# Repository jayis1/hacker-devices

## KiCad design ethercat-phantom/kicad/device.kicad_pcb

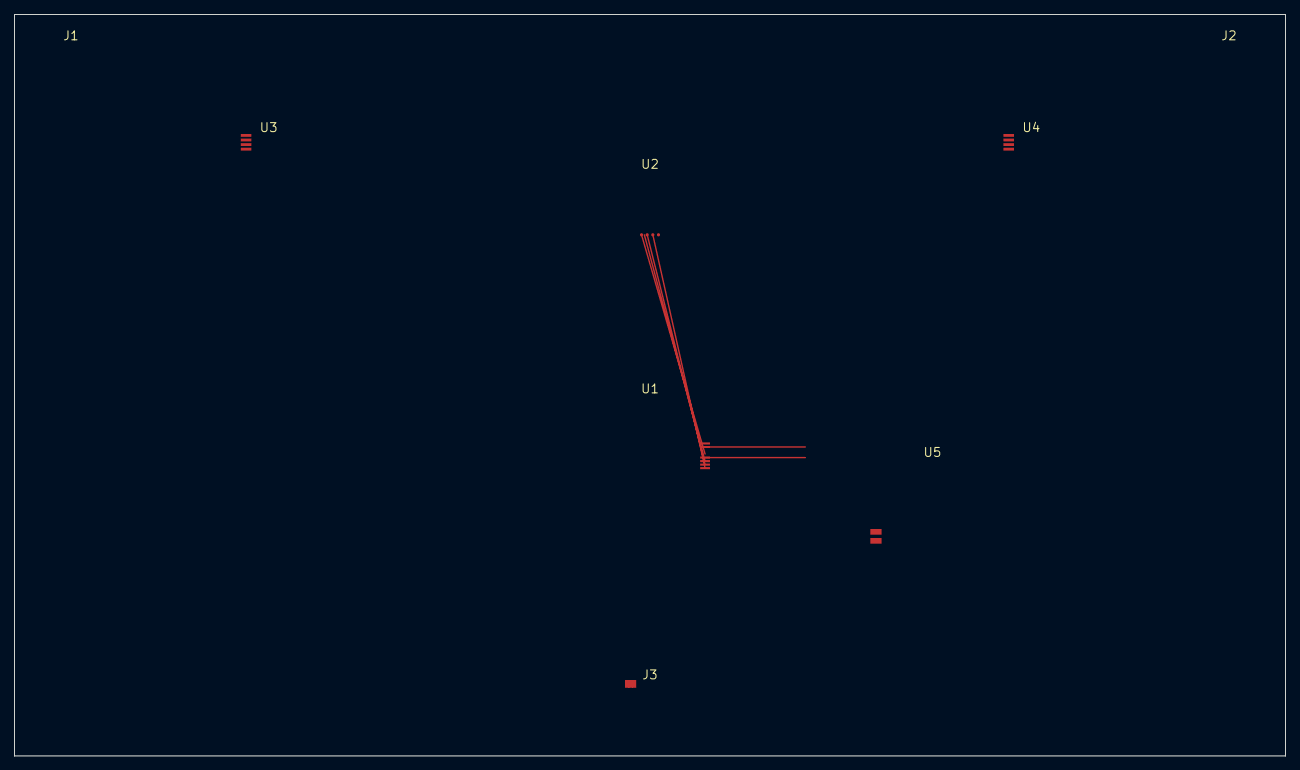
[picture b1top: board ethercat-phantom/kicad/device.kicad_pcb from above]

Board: 2 copper layers, 180.0 x 105.0 mm, 8 parts (0 on the bottom side), 6 nets.

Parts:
J1: Port A; RJ45_Amphenol_RJMG1BD3B8K1ANR
J2: Port B; RJ45_Amphenol_RJMG1BD3B8K1ANR
J3: USB-C Debug/Power; USB_C_Receptacle_HRO_TYPE-C-31-M-12
U1: STM32H753VIT6; LQFP-100_14x14mm_P0.5mm
U2: LFE5U-25F-6BG256C; BGA-256_14.0x14.0mm_Layout16x16_P0.8mm
U3, U4: KSZ8081RNBCA; SSOP-32_5.3x10.2mm_P0.65mm
U5: ESP32-C6-WROOM-1-N8; ESP32-C6-WROOM-1

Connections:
FPGA_CS: U1.64, U2.D10
SPI1_MISO: U1.62, U2.D9
SPI1_MOSI: U1.63, U2.D8
SPI1_SCK: U1.61, U2.D7
UART_RADIO_RX: U1.58, U5.17
UART_RADIO_TX: U1.57, U5.16

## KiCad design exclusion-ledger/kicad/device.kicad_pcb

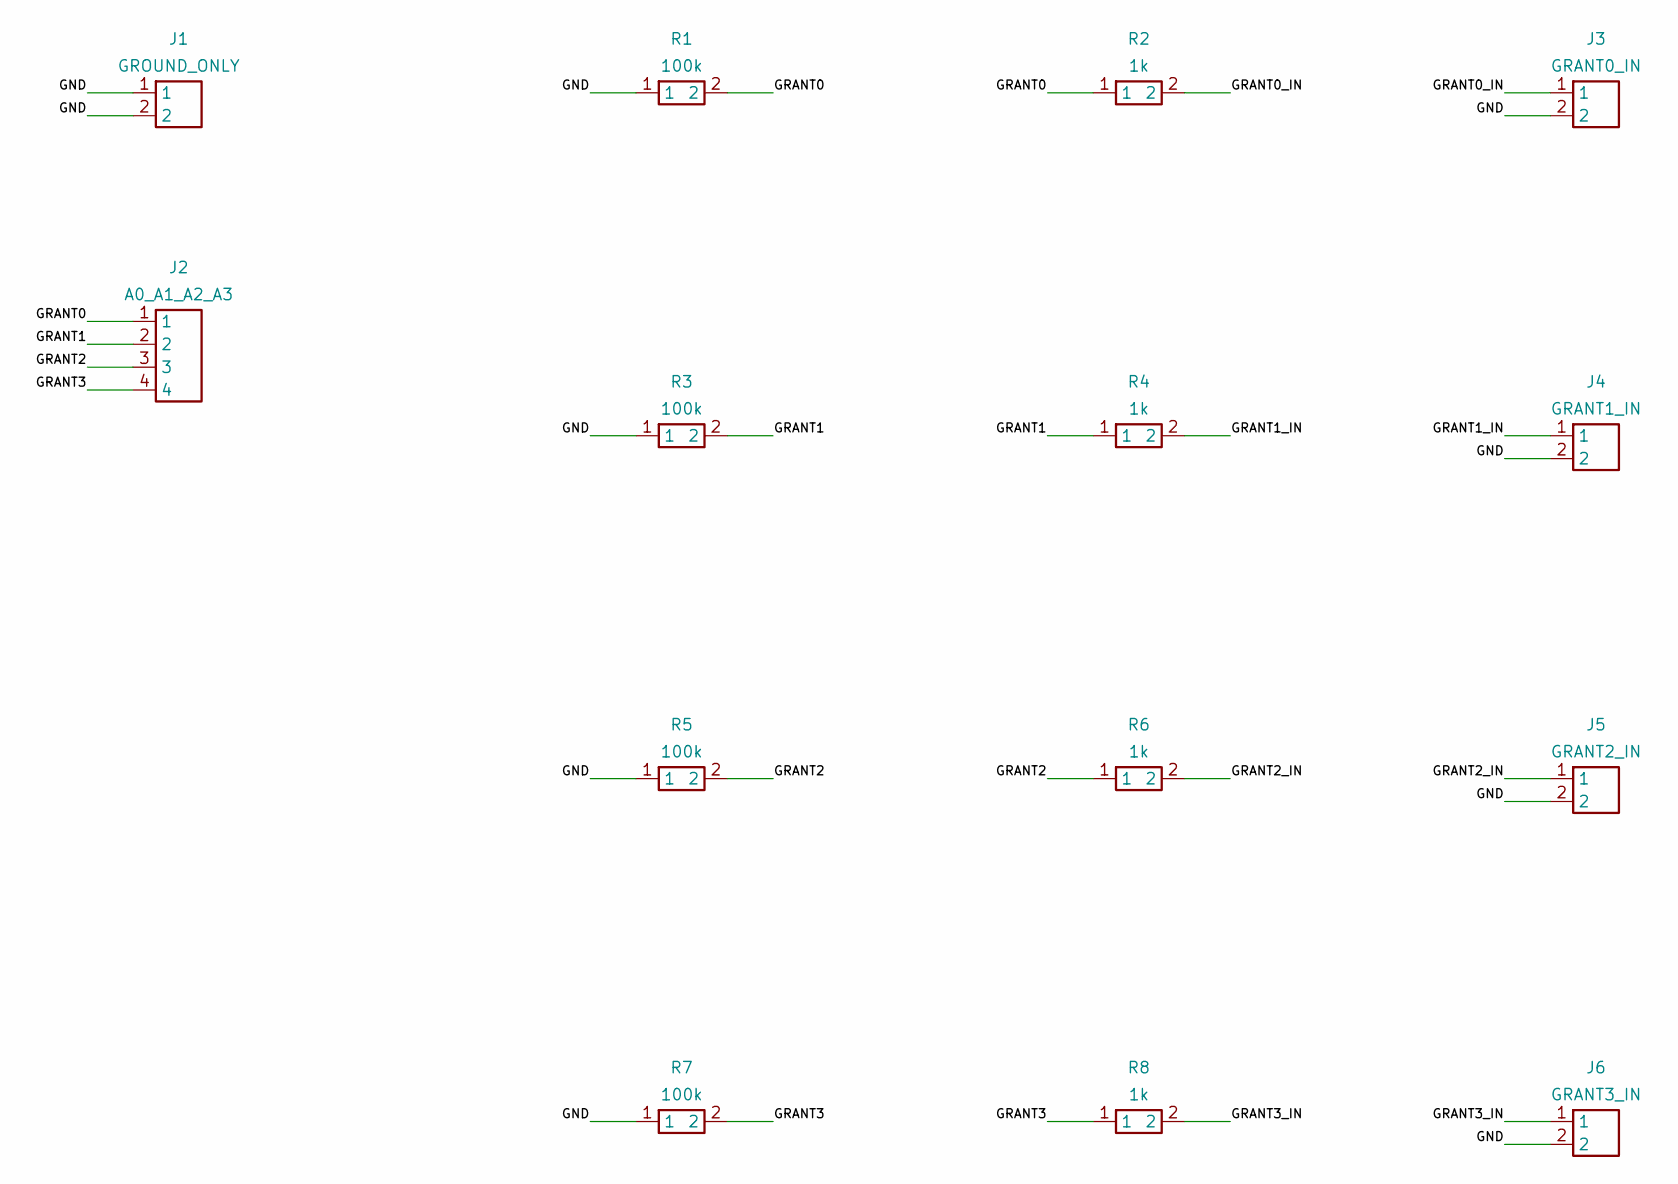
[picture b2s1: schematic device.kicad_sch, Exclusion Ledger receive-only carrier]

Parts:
J1: GROUND_ONLY; PinHeader_1x02_P2.54mm_Vertical
J2: A0_A1_A2_A3; PinHeader_1x04_P2.54mm_Vertical
J3: GRANT0_IN; PinHeader_1x02_P2.54mm_Vertical
J4: GRANT1_IN; PinHeader_1x02_P2.54mm_Vertical
J5: GRANT2_IN; PinHeader_1x02_P2.54mm_Vertical
J6: GRANT3_IN; PinHeader_1x02_P2.54mm_Vertical
R1, R3, R5, R7: 100k; R_Axial_DIN0207_L6.3mm_D2.5mm_P7.62mm_Horizontal
R2, R4, R6, R8: 1k; R_Axial_DIN0207_L6.3mm_D2.5mm_P7.62mm_Horizontal

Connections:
GND: J1.1, J1.2, J3.2, J4.2, J5.2, J6.2, R1.1, R3.1, R5.1, R7.1
GRANT0: J2.1, R1.2, R2.1
GRANT0_IN: J3.1, R2.2
GRANT1: J2.2, R3.2, R4.1
GRANT1_IN: J4.1, R4.2
GRANT2: J2.3, R5.2, R6.1
GRANT2_IN: J5.1, R6.2
GRANT3: J2.4, R7.2, R8.1
GRANT3_IN: J6.1, R8.2

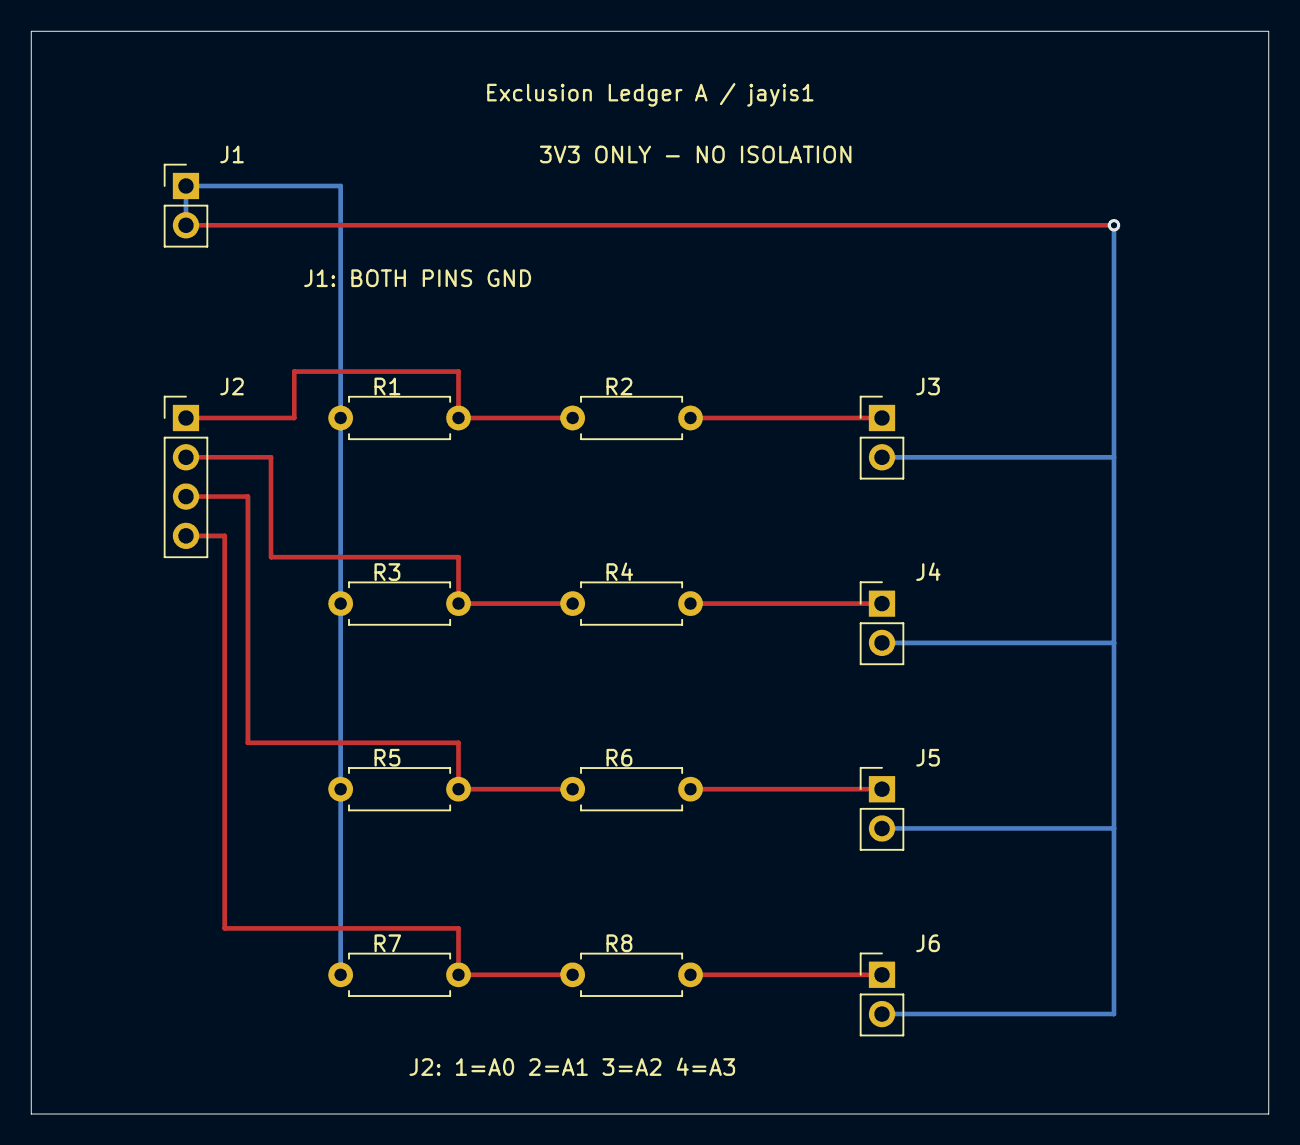
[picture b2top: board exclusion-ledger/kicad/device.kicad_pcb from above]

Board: 2 copper layers, 80.0 x 70.0 mm, 14 parts (0 on the bottom side), 9 nets.

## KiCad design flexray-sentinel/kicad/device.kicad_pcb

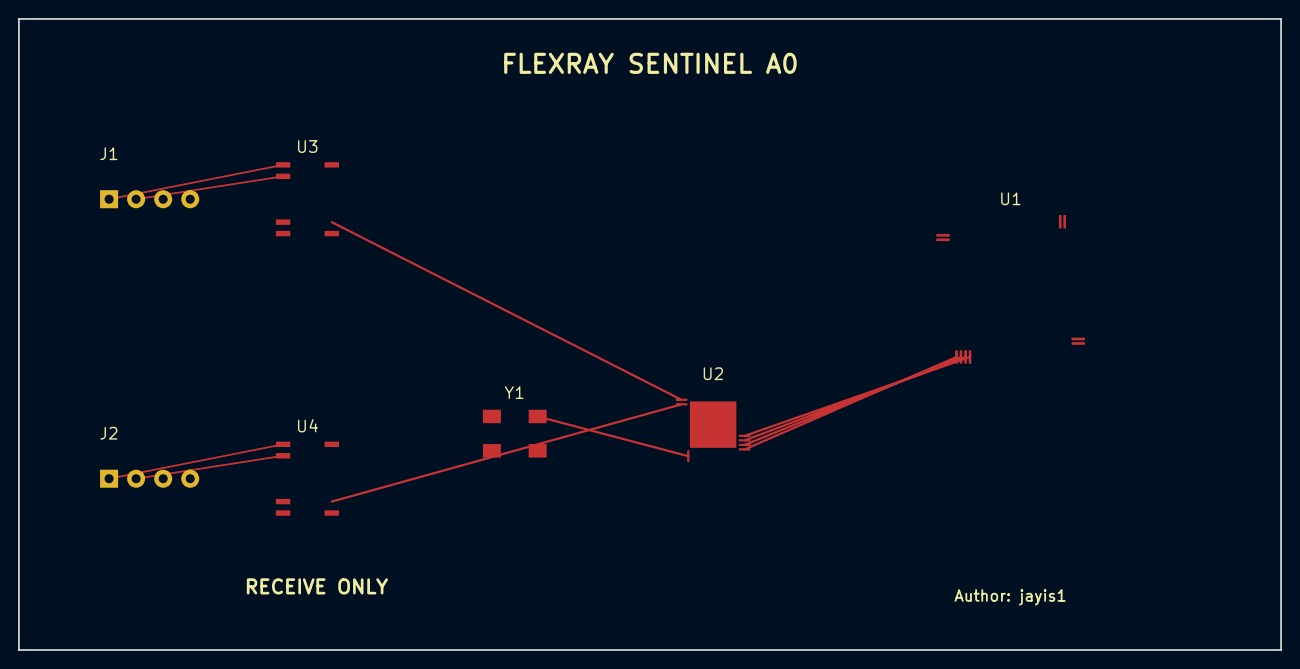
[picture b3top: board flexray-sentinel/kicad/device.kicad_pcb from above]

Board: 2 copper layers, 140.0 x 70.0 mm, 7 parts (0 on the bottom side), 13 nets.

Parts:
J1: CHANNEL A; Molex_Micro-Fit_3.0_43650-0400_1x04_P3.00mm_Horizontal
J2: CHANNEL B; Molex_Micro-Fit_3.0_43650-0400_1x04_P3.00mm_Horizontal
U1: STM32H743VIT6; LQFP-100_14x14mm_P0.5mm
U2: iCE40UP5K-SG48; QFN-48-1EP_7x7mm_P0.5mm_EP5.15x5.15mm
U3: TJA1083 RX A; SOIC-14_3.9x8.7mm_P1.27mm
U4: TJA1083 RX B; SOIC-14_3.9x8.7mm_P1.27mm
Y1: 20MHz TCXO; Oscillator_SMD_Abracon_ASD-4Pin_7.0x5.0mm

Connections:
+3V3: U1.1, U3.14, U4.14, Y1.1, Y1.4
CLK_20M: U2.12, Y1.3
FPGA_SPI_CS: U1.28, U2.27
FPGA_SPI_MISO: U1.26, U2.25
FPGA_SPI_MOSI: U1.27, U2.26
FPGA_SPI_SCK: U1.25, U2.24
FR_A_BM: J1.2, U3.2
FR_A_BP: J1.1, U3.1
FR_A_RX: U2.1, U3.6
FR_B_BM: J2.2, U4.2
FR_B_BP: J2.1, U4.1
FR_B_RX: U2.2, U4.6
GND: J1.3, J1.4, J2.3, J2.4, U1.100, U2.49, U3.7, U3.8, U4.7, U4.8, Y1.2

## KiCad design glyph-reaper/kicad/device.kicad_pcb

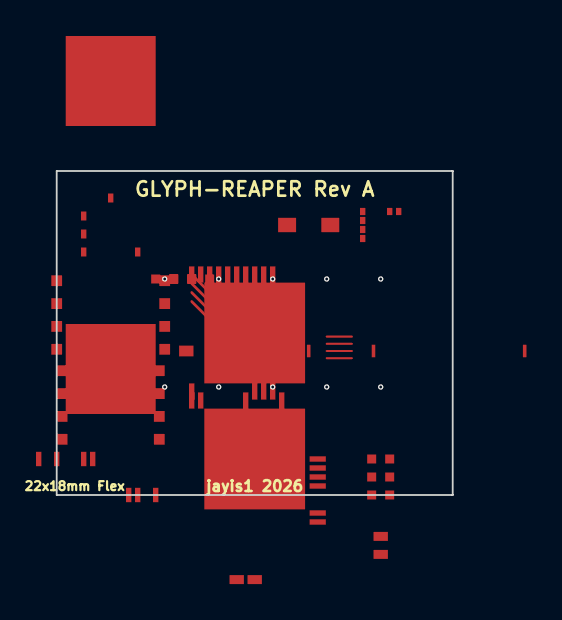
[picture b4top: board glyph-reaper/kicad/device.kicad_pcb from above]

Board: 4 copper layers, 22.0 x 18.0 mm, 18 parts (0 on the bottom side), 16 nets.

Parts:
BT1: CR2032; BatteryHolder_Keystone_3002_1x2032
C3: 100nF; C_0402_1005Metric
C4: 4.7uF; C_0402_1005Metric
C5: 10uF; C_0402_1005Metric
D1: RED; LED_0402_1005Metric
D2: GRN; LED_0402_1005Metric
D3: BLU; LED_0402_1005Metric
J1: DF40C-41DP-0.4V(51); Hirose_DF40C-41DP-0.4V_51_1x41_P0.4mm_Vertical
J3: USB-C; USB_C_Receptacle_Amphenol_10104110
U1: nRF52840-QIAA-R7; QFN-73-1EP_7x7mm_P0.5mm_EP5.6x5.6mm
U2: iCE40UP5K-SG48; QFN-48-1EP_7x7mm_P0.5mm_EP5.6x5.6mm
U3: ESP32-S3-MINI-1
U4: APS6404L-3SQR-SN; SOIC-8_3.9x4.9mm_P1.27mm
U5: W25Q128JVSIQ; SOIC-8_5.275x5.275mm_P1.27mm
U6: TPS62740DSCT; Texas_S-PDSO-N10
U7: LIS2DH12TR; LGA-12_2x2mm_P0.5mm
Y1: 32MHz; Crystal_SMD_2016-2Pin_2.0x1.6mm
Y2: 32.768kHz; Crystal_SMD_3215-2Pin_3.2x1.5mm

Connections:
+3V3: C3.1, C4.1, C5.1, J1.20, U1.1, U1.35, U2.7, U3.2, U3.28, U4.8, U5.8, U6.6, U7.1, U7.2
DISP_CLK_N: J1.3, U2.2
DISP_CLK_P: J1.2, U2.1
FPGA_MISO: U1.10, U2.28
FPGA_MOSI: U1.9, U2.29
FPGA_SCK: U1.8, U2.30
GND: BT1.2, C3.2, C4.2, C5.2, D1.2, D2.2, D3.2, J1.1, J1.41, J3.A1, U1.67, U1.EP, U2.11, U2.EP, U3.1, U3.29, U4.4, U5.4, U6.10, U7.9, U7.10
QSPI_CLK: U4.6, U5.6
QSPI_IO0: U4.5, U5.5
QSPI_IO1: U4.2, U5.2
QSPI_IO2: U4.3, U5.3
QSPI_IO3: U4.7, U5.7
USB_D+: J3.A6, J3.B6, U1.60
USB_D-: J3.A7, J3.B7, U1.59
VBAT: BT1.1, U1.6, U6.1, U6.2
VBUS: J3.A4, J3.B4, U1.58
